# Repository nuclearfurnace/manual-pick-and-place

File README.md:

# manual-pick-and-place
A manual pick-and-place platform for DIY electronics, with an upgrade path.

## the goal
We want a solid pick and place table for manually placing components on prototypes and small runs.

DIY pick and place machines have successfully used off-the-shelf aluminum extrusions and linear guides/bearings to build rigid platforms that are suitable for precise work, even down to 0402 components.  There is a wide gulf, however, between manual set-ups and automatic/CNC machines.

Most manual setups involve tweezers or vacuum pens, which open up issues like gripping parts, dropping parts, dragging your hand across the board, etc. Even "advanced" manual setups are usually cobbled together, with parts you buy from a Home Depot or Lowes.

Our goal is to build a manual pick and place machine that has all the benefits of a CNC-enabled design -- modular, rigid, precise -- while staying simple enough to be usable by hand.  By using the same basic components as its CNC-enabled brethren, like aluminum extrusions and linear bearings, we can design a pick and place table that is capable of being upgraded to full auto in the future.

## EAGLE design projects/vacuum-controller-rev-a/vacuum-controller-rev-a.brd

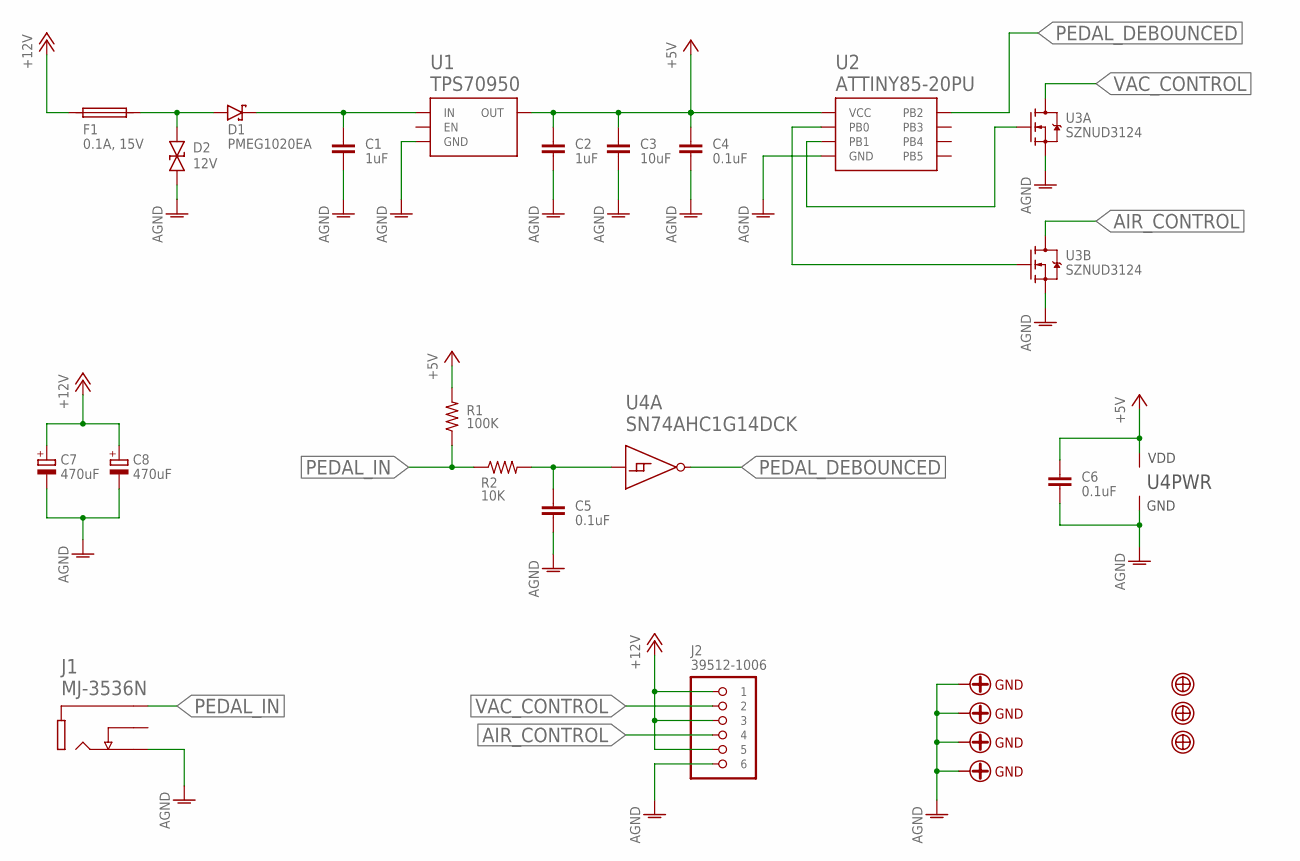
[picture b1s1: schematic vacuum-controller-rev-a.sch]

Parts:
C1, C2: 1uF; C0603
C3: 10uF; C0805
C4, C5, C6: 0.1uF; C0402
C7, C8: 470uF; RADIAL-D8-P3.5-PD0.5
D1: PMEG1020EA; SOD323-R
D2: 12V; SMA
F1: 0.1A, 15V; C0805
J1: MJ-3536N
J2: 39512-1006
R1: 100K; R0402
R2: 10K; R0402
U1: TPS70950; R-PDSO-G5-DBV
U2: ATTINY85-20PU; PDIP-8
U3: SZNUD3124; SOT-457
U4: SN74AHC1G14DCK; R-PDSO-G5-DCK
U$1, U$2, U$3, U$4: SCREW-THRU-GND-#4
U$5, U$6, U$7: FIDUCIAL-1MM; FIDUCIAL_1MM

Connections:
+5V: C2.1, C3.1, C4.1, C6.1, R1.2, U1.5 (OUT), U2.P$8 (VCC), U4.5 (VDD)
+12V: C7.+, C8.+, F1.1, J2.P$1 (1), J2.P$3 (3), J2.P$5 (5)
AGND: C1.2, C2.2, C3.2, C4.2, C5.2, C6.2, C7.-, C8.-, D2.A, J1.P$2, J2.P$6 (6), U1.2 (GND), U2.P$4 (GND), U3.1 (S), U3.4 (S), U4.3 (GND), U$1.P$1, U$1.P$2, U$1.P$3, U$1.P$4, U$1.P$5, U$1.P$6, U$1.P$7, U$1.P$8, U$1.P$9, U$2.P$1, U$2.P$2, U$2.P$3, U$2.P$4, U$2.P$5, U$2.P$6, U$2.P$7, U$2.P$8, U$2.P$9, U$3.P$1, U$3.P$2, U$3.P$3, U$3.P$4, U$3.P$5, U$3.P$6, U$3.P$7, U$3.P$8, U$3.P$9, U$4.P$1, U$4.P$2, U$4.P$3, U$4.P$4, U$4.P$5, U$4.P$6, U$4.P$7, U$4.P$8, U$4.P$9
AIR_CONTROL: J2.P$4 (4), U3.3 (D)
unnamed: C1.1, D1.C, U1.1 (IN)
unnamed: D1.A, D2.C, F1.2
unnamed: C5.1, R2.2, U4.2 (A)
unnamed: U2.P$6 (PB1), U3.2 (G)
unnamed: U2.P$5 (PB0), U3.5 (G)
PEDAL_DEBOUNCED: U2.P$7 (PB2), U4.4 (Y)
PEDAL_IN: J1.P$1, R1.1, R2.1
VAC_CONTROL: J2.P$2 (2), U3.6 (D)

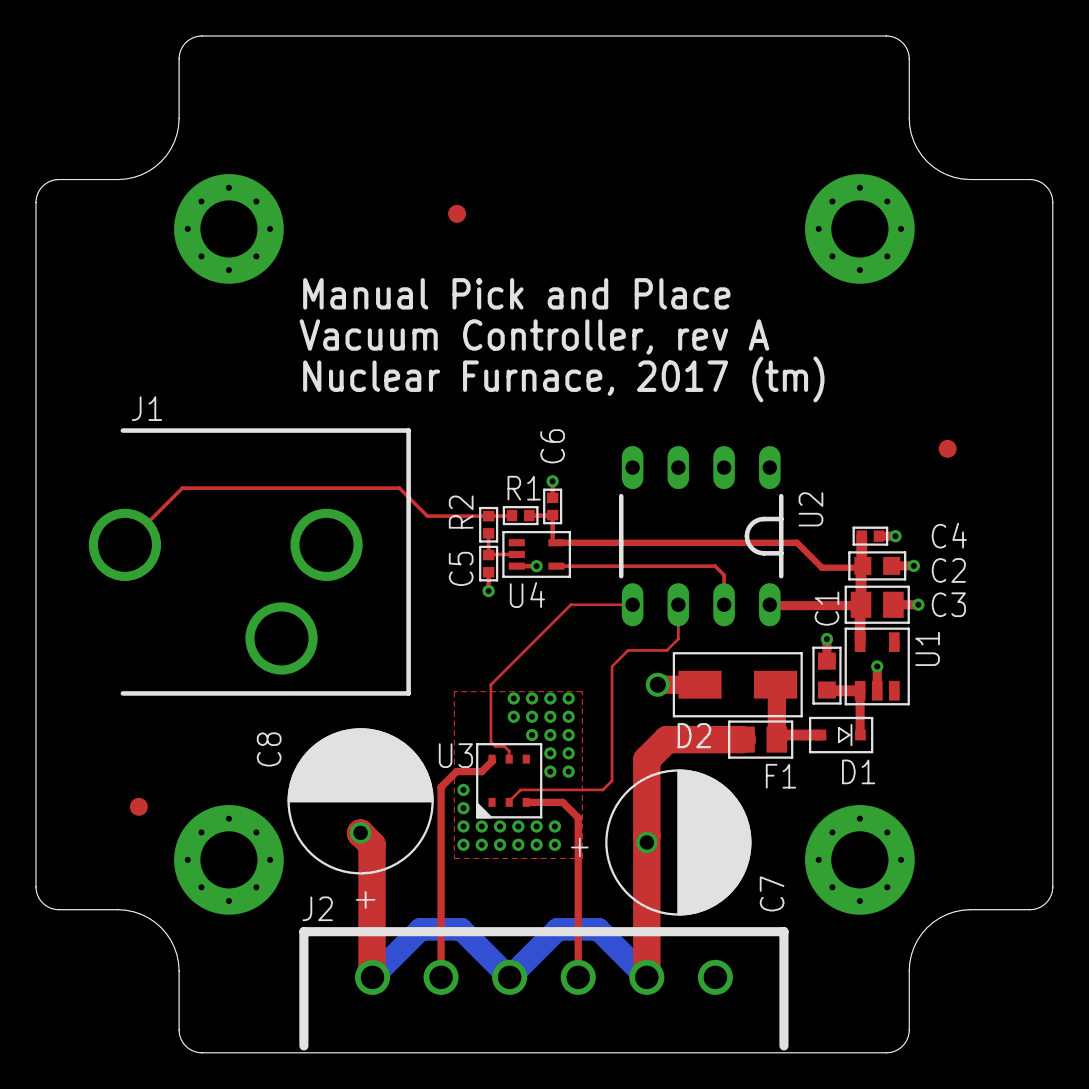
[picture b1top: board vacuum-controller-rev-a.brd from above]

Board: 2 copper layers, 56.5 x 56.5 mm, 26 parts (0 on the bottom side), 12 nets.

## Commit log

2017-04-14 :space_invader: Added .gitattributes & .gitignore files
2017-04-14 Initial commit!
    Most of the pick and place is roughly put together. The biggest things
    that remain:
    - tweaking dimensions of machined parts as pieces arrive and are test
    fit
    - adding fasteners (mates only at the moment)
    - adding proper costing (since we have it for everything minus machined
2017-04-15 Massive reorganization + adding lots of fasteners.
    I've tried to organize almost everything in functional subassemblies, as
    well as moving the actual part/assembly files into appropriate folders:
    there's a folder for custom parts I'm machining, and a folder for
    off-the-shelf (even if we modify them) parts.
    The biggest downside to the subassembly approach is that it seems to put
    the kibosh on moving components from the top-level assembly., whereas
2017-04-17 Added proper materials and costing for all components.
    All parts now have a material and cost set. Some quirks:
    - SolidWorks doesn't have every specific material, so some of them are
    fudged (18-8 SS becomes 304, all non-10XX steel becomes alloy steel,
    etc)
    - soemn of the parts are custom, but trivial, so I gave them a "how much
    a machinist friend might charge" sort of price
2017-05-03 Add the vacuum controller board to the repo.
    This board will take the foot pedal switch input and control the opening
    and closing of the vacuum valve and air valve to properly sequence the
    removal of vacuum/application of air to quickly drop a part without
    dragging it back up after positioning.
2017-05-03 Small tweaks here and there; added custom designed end stops for the rails.
2017-05-04 Starting to tweak the board layout to better suit the enclosure, as well as getting the 3D models of the connectors.
2017-05-04 More tweaks to the enclosure to match up to the altered board layout.
    The terminal block is now nearly flush with the outside of the case for
    full plug engagement. The mono phono jack is also nearly flush, and has
    a properly sized hole to let it get very close.
2017-05-11 Many changes to the schematic/board.
    - added part numbers to all components
    - added 2x470uF electrolytic caps to smooth the 12V rail during relay
    switching events
    - switched to a DIP-8 footprint for the ATtiny so we can program it in a
    cheapo programmer and not have to mess around with SOIC clips and all
    that
2017-05-13 Firm up the placement bed and nozzle shaft depth.
    Firmed up the dimensions (aka the thickness) of the placement bed, and
    adjusted the circlip grooves on the nozzle shaft to properly place the
    head offset the desired amount from the bed.
2017-05-15 Add the graphics files for the cover overlay.
2017-05-15 Add the TIF version, too.
2017-05-15 Add a proper transparency mask.
2017-05-15 Add the cover panel/decal/whatever-you-want-to-call-it to the enclosure.
    Now we know what pins do what!
2017-05-16 Add in the first cut off software for the vacuum controller.
    We have some bog-standard ANSI C targetting the AVR library to control
    the ATtiny and blip the valves and all of that.
    Right now, it's configured that it recognizes the momentary blips from
    the pedal, and does the following:
    - if the vacuum is not applied, it applies it and leaves it on
    - if the vacuum is applied, it turns it off and briefly opens the air
2017-06-06 Some small tweaks to the grounding for the load driver.
2017-06-06 Add the proper direction marking for D1.
2017-09-04 Fix up the Makefile so that we can easily flash the firmware.
